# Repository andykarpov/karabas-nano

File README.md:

# Karabas-Nano

**Yet another ZX Spectrum clone ;)**

## Intro

ZX Spectrum compatible machine with real **Z80** CPU and all logic inside the CPLD Altera **EPM3256ATC144** (or EPM7512).

## The idea

The idea was to learn KiCAD and make a **cheapest** and **smallest** ZX Spectrum clone with minimum components and real CPU. 
Some parts of this schematics are grabbed from the **Karabas-128** and **ZX-UNO** projects (like RGB DAC, PAL coder, Tape-in logic).
The heart of this project is a real SMD Z80 CPU and ULA implementation on Altera CPLD EPM3256ATC144. 

## Firmwares

The board contains an SD card socket, so at least 2 different configurations are supported:

1) Z-Controller based configuration (Pentagon timings, GLUK reset service in the ROM bank 0, 1024kB of extended memory via port #DFFD (Profi))

2) DivMMC based configuration (Pentagon timings, ESXDOS 0.8.7 in the ROM bank 0, 128kB of memory)

## More info

**ERRATA for PCB rev.A:** [Russian](https://github.com/andykarpov/karabas-nano/blob/master/ERRATA_revA.md).

**ERRATA for PCB rev.B:** [Russian](https://github.com/andykarpov/karabas-nano/blob/master/ERRATA_revB.md).

**Latest revision:** rev.I.

License for this project is **WTFPL**. [More details here](https://github.com/andykarpov/karabas-nano/blob/master/LICENSE.md).

### Pre-production renders

### PCB Rev. H assembly example by [Xoomoh (Михайло Капітанов)](https://github.com/xoomoh/)

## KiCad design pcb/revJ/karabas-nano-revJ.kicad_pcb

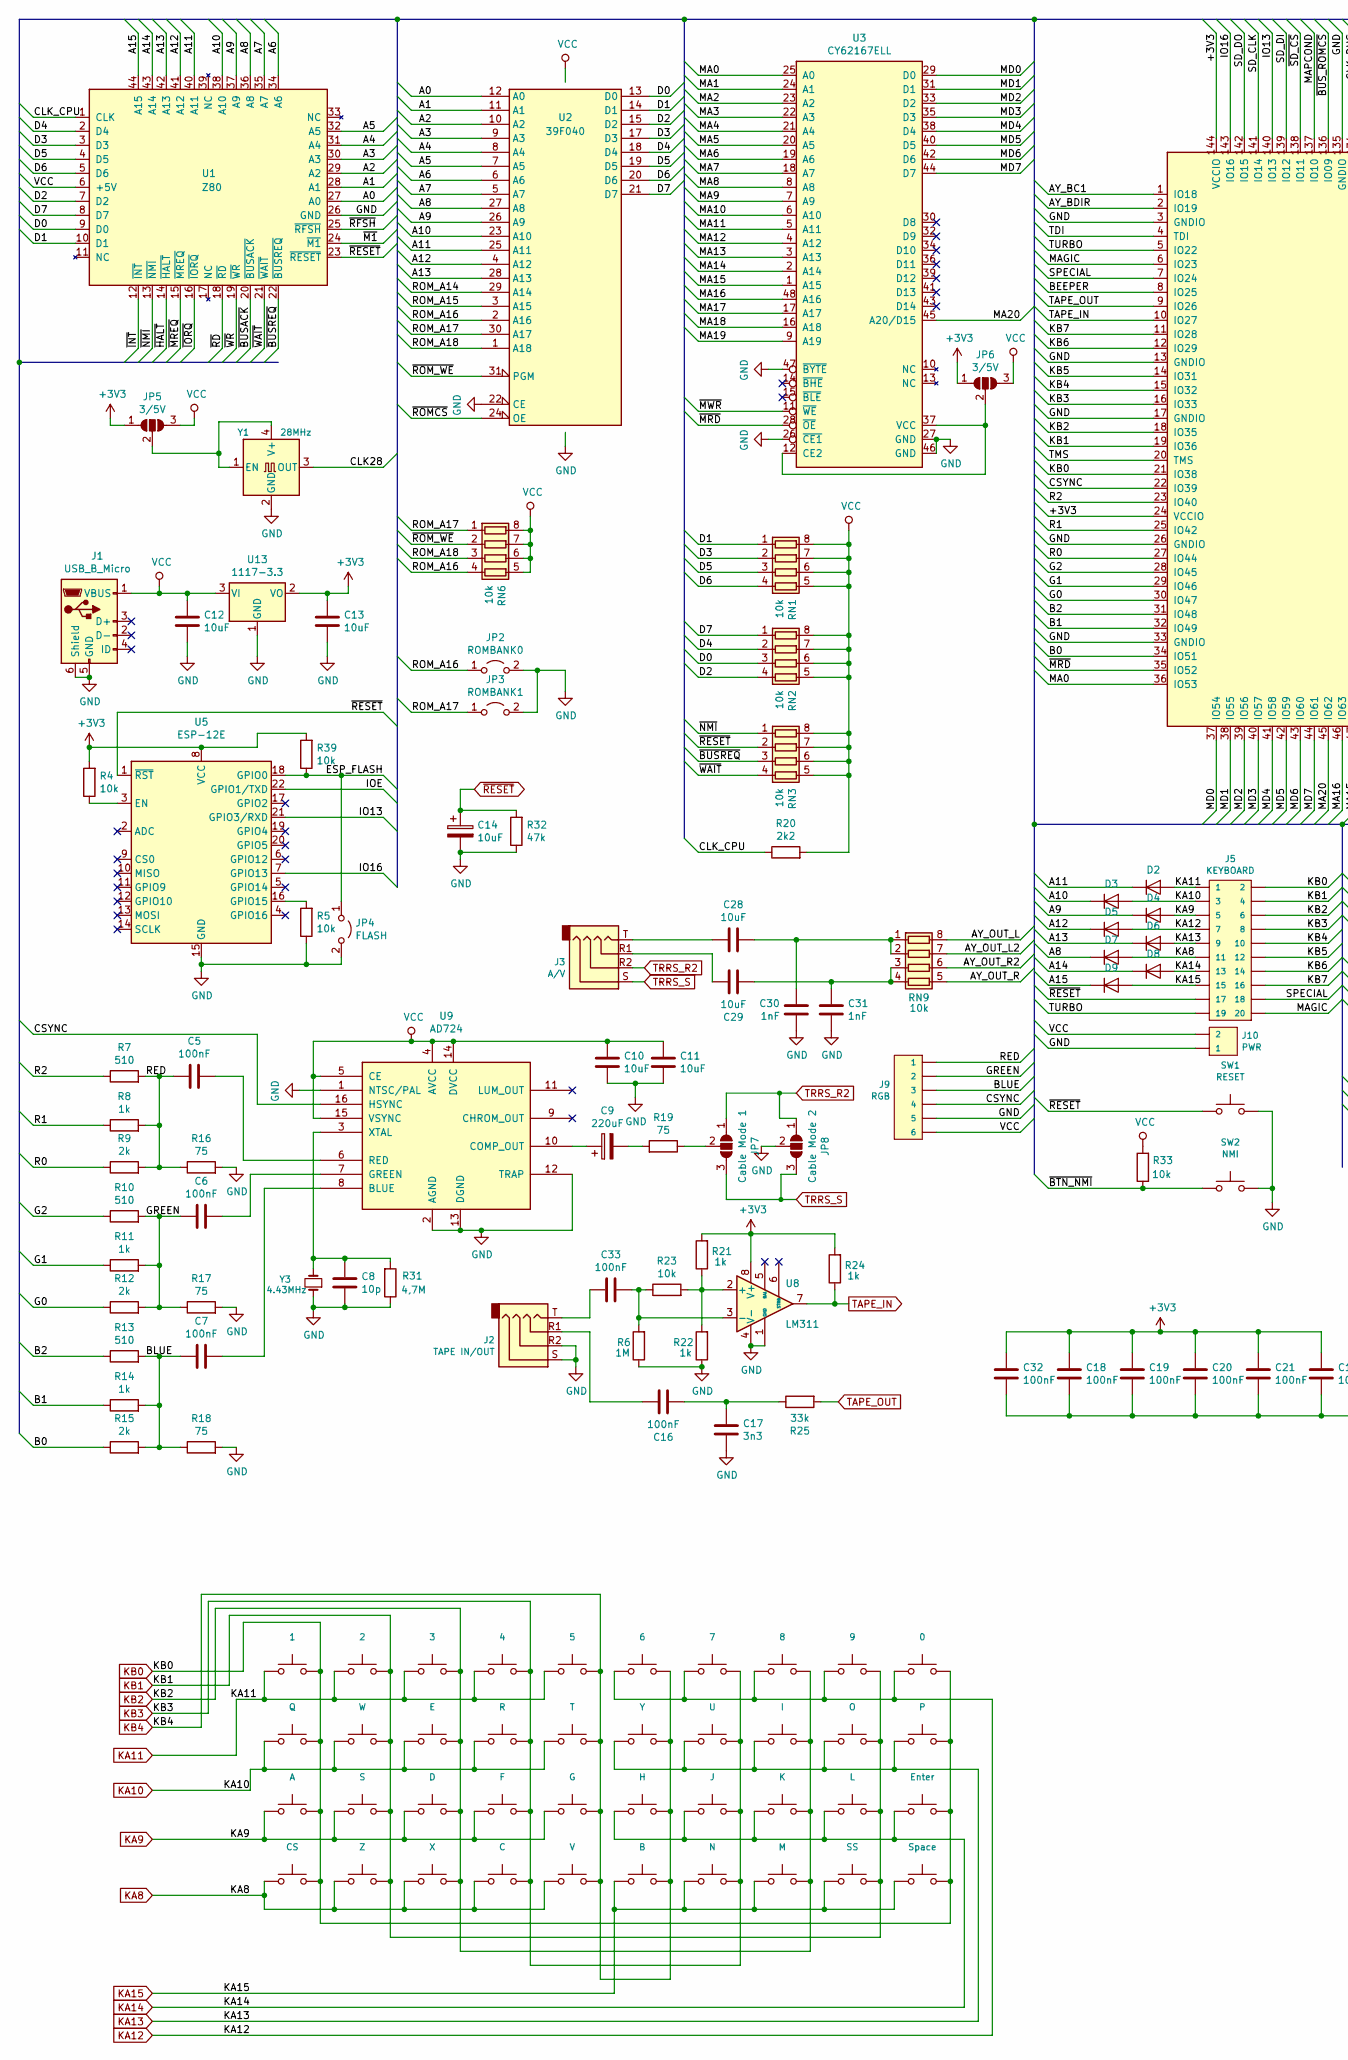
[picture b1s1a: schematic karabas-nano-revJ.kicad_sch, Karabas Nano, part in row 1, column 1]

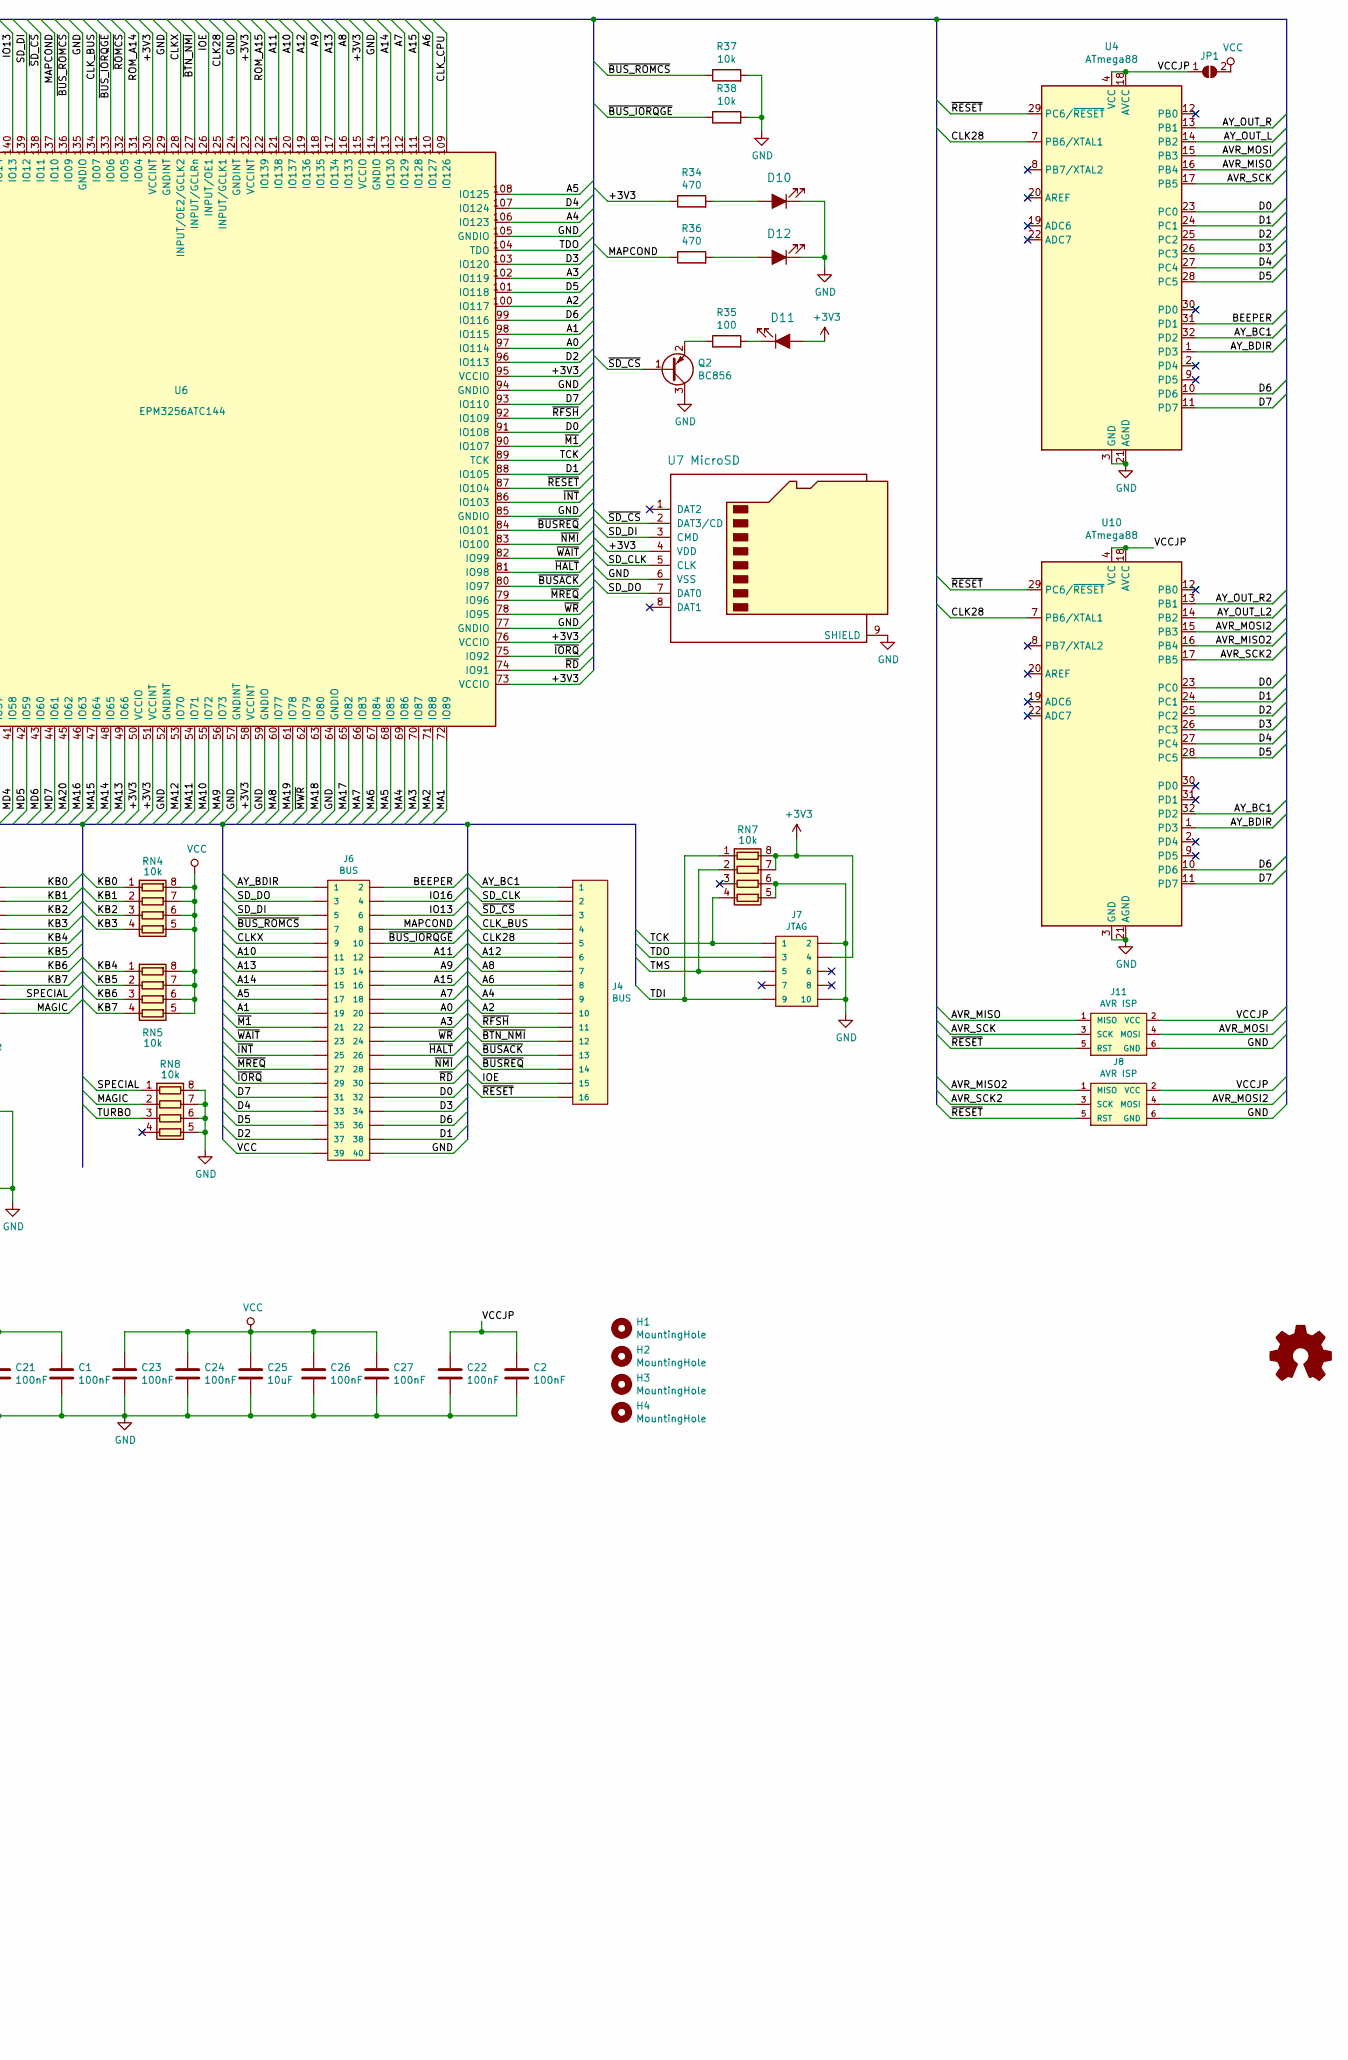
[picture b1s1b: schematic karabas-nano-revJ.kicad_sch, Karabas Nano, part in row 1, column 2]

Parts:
C1, C2, C5, C6, C7, C16, C18, C19, C20, C21, C22, C23, C24, C26, C27, C32, C33: 100nF; C_0805_2012Metric
C8: 10p; C_0805_2012Metric
C9: 220uF; CP_EIA-7343-31_Kemet-D_Pad2.25x2.55mm_HandSolder
C10, C11, C12, C13, C25, C28, C29: 10uF; C_0805_2012Metric
C14: 10uF; CP_EIA-3528-21_Kemet-B_Pad1.50x2.35mm_HandSolder
C17: 3n3; C_0805_2012Metric
C30, C31: 1nF; C_0805_2012Metric
D2, D3, D4, D5, D6, D7, D8, D9: 1N4148W; D_SOD-123
D10: PWR; LED_0805_2012Metric_Pad1.15x1.40mm_HandSolder; MPN LG R971-KN-1; Digi-Key_PN 475-1410-1-ND
D11: SD; LED_0805_2012Metric_Pad1.15x1.40mm_HandSolder; MPN LH R974-LP-1; Digi-Key_PN 475-1415-1-ND
D12: MMC; LED_0805_2012Metric_Pad1.15x1.40mm_HandSolder; MPN LH R974-LP-1; Digi-Key_PN 475-1415-1-ND
H1, H2, H3, H4: MountingHole; MountingHole_2.7mm_M2.5_Pad
J1: USB_B_Micro; USB_Micro-B_Amphenol_10118194_Horizontal
J2: TAPE IN/OUT; AUDIO_JACK_3.5MM_SMD_TRRS_rounded_mixed
J3: A/V; AUDIO_JACK_3.5MM_SMD_TRRS_rounded_mixed
J4: BUS; PinHeader_1x16_P2.54mm_Vertical
J5: KEYBOARD; PinHeader_2x10_P2.54mm_Vertical
J6: BUS; PinHeader_2x20_P2.54mm_Vertical
J7: JTAG; PinHeader_2x05_P2.54mm_Vertical
J8, J11: AVR ISP; PinHeader_2x03_P2.54mm_Vertical
J9: RGB; PinHeader_1x06_P2.54mm_Vertical
J10: PWR; PinHeader_1x02_P2.54mm_Vertical
JP1: SolderJumper_2_Open; SolderJumper-2_P1.3mm_Open_TrianglePad1.0x1.5mm
JP2: ROMBANK0; PinHeader_1x02_P2.54mm_Vertical
JP3: ROMBANK1; PinHeader_1x02_P2.54mm_Vertical
JP4: FLASH; PinHeader_1x02_P2.54mm_Vertical
JP5, JP6: 3/5V; SolderJumper-3_P1.3mm_Open_RoundedPad1.0x1.5mm
JP7: Cable Mode 1; SolderJumper-3_P1.3mm_Open_RoundedPad1.0x1.5mm
JP8: Cable Mode 2; SolderJumper-3_P1.3mm_Open_RoundedPad1.0x1.5mm
Q2: BC856; SOT-23
R4, R5, R23, R33, R37, R38, R39: 10k; R_0805_2012Metric
R6: 1M; R_0805_2012Metric
R7, R10, R13: 510; R_0805_2012Metric
R8, R11, R14, R21, R22, R24: 1k; R_0805_2012Metric
R9, R12, R15: 2k; R_0805_2012Metric
R16, R17, R18, R19: 75; R_0805_2012Metric
R20: 2k2; R_0805_2012Metric
R25: 33k; R_0805_2012Metric
R31: 4,7M; R_0805_2012Metric
R32: 47k; R_0805_2012Metric
R34, R36: 470; R_0805_2012Metric
R35: 100; R_0805_2012Metric
RN1, RN2, RN3, RN4, RN5, RN6, RN7, RN8, RN9: 10k; R_Array_Convex_4x0612
SW1: RESET; small-btn
SW2: NMI; small-btn
SW3: 1; small-btn
SW4: 2; small-btn
SW5: 3; small-btn
SW6: 4; small-btn
SW7: 5; small-btn
SW8: 6; small-btn
SW9: 7; small-btn
SW10: 8; small-btn
SW11: 9; small-btn
SW12: 0; small-btn
SW13: Q; small-btn
SW14: A; small-btn
SW15: CS; small-btn
SW16: W; small-btn
SW17: S; small-btn
SW18: Z; small-btn
SW19: E; small-btn
SW20: D; small-btn
SW21: X; small-btn
SW22: R; small-btn
SW23: F; small-btn
SW24: C; small-btn
SW25: T; small-btn
SW26: G; small-btn
SW27: V; small-btn
SW28: Y; small-btn
SW29: H; small-btn
SW30: B; small-btn
SW31: U; small-btn
SW32: J; small-btn
SW33: N; small-btn
SW34: I; small-btn
SW35: K; small-btn
SW36: M; small-btn
SW37: O; small-btn
SW38: L; small-btn
SW39: SS; small-btn
SW40: P; small-btn
SW41: Enter; small-btn
SW42: Space; small-btn
U1: Z80; TQFP-44_14x14mm_P0.8mm
U2: 39F040; PLCC-32_11.4x14.0mm_P1.27mm-bigpads
U3: CY62167ELL; TSOP-I-48_18.4x12mm_P0.5mm
U4, U10: ATmega88; TQFP-32_7x7mm_P0.8mm
U5: ESP-12E
U6: EPM3256ATC144; LQFP-144_20x20mm_P0.5mm
U7: MicroSD; Conn_uSDcard
U8: LM311; SO-8_3.9x4.9mm_P1.27mm
U9: AD724; SOIC-16W_7.5x10.3mm_P1.27mm
U13: 1117-3.3; SOT-223-3_TabPin2
Y1: 28MHz; Oscillator_SMD_EuroQuartz_XO91-4Pin_7.0x5.0mm
Y3: 4.43MHz; Crystal_HC49-U_Vertical

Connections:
+3V3: C1.2, C13.2, C18.2, C19.2, C20.2, C21.2, C32.2, D11.2 (A), J7.4, JP5.1 (A), JP6.1 (A), R4.2, R21.2, R24.2, R34.1, R39.2, RN7.7 (R2.2), RN7.8 (R1.2), U5.8 (VCC), U6.24 (VCCIO), U6.50 (VCCIO), U6.51 (VCCINT), U6.58 (VCCINT), U6.73 (VCCIO), U6.76 (VCCIO), U6.95 (VCCIO), U6.115 (VCCIO), U6.123 (VCCINT), U6.130 (VCCINT), U6.144 (VCCIO), U7.4 (VDD), U8.8 (V+), U13.2 (VO)
/A0: J6.20, U1.27 (A0), U2.12 (A0), U6.97 (IO114)
/A1: J6.19, U1.28 (A1), U2.11 (A1), U6.98 (IO115)
/A2: J4.10, U1.29 (A2), U2.10 (A2), U6.100 (IO117)
/A3: J6.22, U1.30 (A3), U2.9 (A3), U6.102 (IO119)
/A4: J4.9, U1.31 (A4), U2.8 (A4), U6.106 (IO123)
/A5: J6.17, U1.32 (A5), U2.7 (A5), U6.108 (IO125)
/A6: J4.8, U1.34 (A6), U2.6 (A6), U6.110 (IO127)
/A7: J6.18, U1.35 (A7), U2.5 (A7), U6.112 (IO129)
/A8: D7.1 (K), J4.7, U1.36 (A8), U2.27 (A8), U6.116 (IO133)
/A9: D4.1 (K), J6.14, U1.37 (A9), U2.26 (A9), U6.118 (IO135)
/A10: D3.1 (K), J6.11, U1.38 (A10), U2.23 (A10), U6.120 (IO137)
/A11: D2.1 (K), J6.12, U1.40 (A11), U2.25 (A11), U6.121 (IO138)
/A12: D5.1 (K), J4.6, U1.41 (A12), U2.4 (A12), U6.119 (IO136)
/A13: D6.1 (K), J6.13, U1.42 (A13), U2.28 (A13), U6.117 (IO134)
/A14: D8.1 (K), J6.15, U1.43 (A14), U6.113 (IO130)
/A15: D9.1 (K), J6.16, U1.44 (A15), U6.111 (IO128)
/AVR_MISO: J11.1 (MISO), U4.16 (PB4)
/AVR_MISO2: J8.1 (MISO), U10.16 (PB4)
/AVR_MOSI: J11.4 (MOSI), U4.15 (PB3)
/AVR_MOSI2: J8.4 (MOSI), U10.15 (PB3)
/AVR_SCK: J11.3 (SCK), U4.17 (PB5)
/AVR_SCK2: J8.3 (SCK), U10.17 (PB5)
/AY_BC1: J4.1, U4.32 (PD2), U6.1 (IO18), U10.32 (PD2)
/AY_BDIR: J6.1, U4.1 (PD3), U6.2 (IO19), U10.1 (PD3)
/AY_OUT_L: RN9.8 (R1.2), U4.14 (PB2)
/AY_OUT_L2: RN9.7 (R2.2), U10.14 (PB2)
/AY_OUT_R: RN9.5 (R4.2), U4.13 (PB1)
/AY_OUT_R2: RN9.6 (R3.2), U10.13 (PB1)
/B0: R15.1, U6.34 (IO51)
/B1: R14.1, U6.32 (IO49)
/B2: R13.1, U6.31 (IO48)
/BEEPER: J6.2, U4.31 (PD1), U6.8 (IO25)
/BLUE: C7.2, J9.3, R13.2, R14.2, R15.2, R18.1
/CLK28: J4.5, U4.7 (PB6/XTAL1), U6.125 (INPUT/GCLK1), U10.7 (PB6/XTAL1), Y1.3 (OUT)
/CLKX: J6.9, U6.128 (INPUT/OE2/GCLK2)
/CLK_BUS: J4.4, U6.134 (IO07)
/CLK_CPU: R20.1, U1.1 (CLK), U6.109 (IO126)
/CSYNC: J9.4, U6.22 (IO39), U9.16 (HSYNC)
/D0: J6.32, RN2.3 (R3.1), U1.9 (D0), U2.13 (D0), U4.23 (PC0), U6.91 (IO108), U10.23 (PC0)
/D1: J6.38, RN1.1 (R1.1), U1.10 (D1), U2.14 (D1), U4.24 (PC1), U6.88 (IO105), U10.24 (PC1)
/D2: J6.37, RN2.4 (R4.1), U1.7 (D2), U2.15 (D2), U4.25 (PC2), U6.96 (IO113), U10.25 (PC2)
/D3: J6.34, RN1.2 (R2.1), U1.3 (D3), U2.17 (D3), U4.26 (PC3), U6.103 (IO120), U10.26 (PC3)
/D4: J6.33, RN2.2 (R2.1), U1.2 (D4), U2.18 (D4), U4.27 (PC4), U6.107 (IO124), U10.27 (PC4)
/D5: J6.35, RN1.3 (R3.1), U1.4 (D5), U2.19 (D5), U4.28 (PC5), U6.101 (IO118), U10.28 (PC5)
/D6: J6.36, RN1.4 (R4.1), U1.5 (D6), U2.20 (D6), U4.10 (PD6), U6.99 (IO116), U10.10 (PD6)
/D7: J6.31, RN2.1 (R1.1), U1.8 (D7), U2.21 (D7), U4.11 (PD7), U6.93 (IO110), U10.11 (PD7)
/ESP_FLASH: JP4.1 (A), R39.1, U5.18 (GPIO0)
/G0: R12.1, U6.30 (IO47)
/G1: R11.1, U6.29 (IO46)
/G2: R10.1, U6.28 (IO45)
/GREEN: C6.2, J9.2, R10.2, R11.2, R12.2, R17.1
/IO13: J6.6, U5.21 (GPIO3/RXD), U6.140 (IO13)
/IO16: J6.4, U5.7 (GPIO13), U6.143 (IO16)
/IOE: J4.15, U5.22 (GPIO1/TXD), U6.126 (INPUT/OE1)
/KB5: J5.12, RN5.2 (R2.1), U6.14 (IO31)
/KB6: J5.14, RN5.3 (R3.1), U6.12 (IO29)
/KB7: J5.16, RN5.4 (R4.1), U6.11 (IO28)
/MA0: U3.25 (A0), U6.36 (IO53)
/MA1: U3.24 (A1), U6.72 (IO89)
/MA2: U3.23 (A2), U6.71 (IO88)
/MA3: U3.22 (A3), U6.70 (IO87)
/MA4: U3.21 (A4), U6.69 (IO86)
/MA5: U3.20 (A5), U6.68 (IO85)
/MA6: U3.19 (A6), U6.67 (IO84)
/MA7: U3.18 (A7), U6.66 (IO83)
/MA8: U3.8 (A8), U6.60 (IO77)
/MA9: U3.7 (A9), U6.56 (IO73)
/MA10: U3.6 (A10), U6.55 (IO72)
/MA11: U3.5 (A11), U6.54 (IO71)
/MA12: U3.4 (A12), U6.53 (IO70)
/MA13: U3.3 (A13), U6.49 (IO66)
/MA14: U3.2 (A14), U6.48 (IO65)
/MA15: U3.1 (A15), U6.47 (IO64)
/MA16: U3.48 (A16), U6.46 (IO63)
/MA17: U3.17 (A17), U6.65 (IO82)
/MA18: U3.16 (A18), U6.63 (IO80)
/MA19: U3.9 (A19), U6.61 (IO78)
/MA20: U3.45 (A20/D15), U6.45 (IO62)
/MAGIC: J5.20, RN8.2 (R2.1), U6.6 (IO23)
/MAPCOND: J6.8, R36.1, U6.137 (IO10)
/MD0: U3.29 (D0), U6.37 (IO54)
/MD1: U3.31 (D1), U6.38 (IO55)
/MD2: U3.33 (D2), U6.39 (IO56)
/MD3: U3.35 (D3), U6.40 (IO57)
/MD4: U3.38 (D4), U6.41 (IO58)
/MD5: U3.40 (D5), U6.42 (IO59)
/MD6: U3.42 (D6), U6.43 (IO60)
/MD7: U3.44 (D7), U6.44 (IO61)
/R0: R9.1, U6.27 (IO44)
/R1: R8.1, U6.25 (IO42)
/R2: R7.1, U6.23 (IO40)
/RED: C5.2, J9.1, R7.2, R8.2, R9.2, R16.1
/ROM_A14: U2.29 (A14), U6.131 (IO04)
/ROM_A15: U2.3 (A15), U6.122 (IO139)
/ROM_A16: JP2.1 (A), RN6.4 (R4.1), U2.2 (A16)
/ROM_A17: JP3.1 (A), RN6.1 (R1.1), U2.30 (A17)
/ROM_A18: RN6.3 (R3.1), U2.1 (A18)
/SD_CLK: J4.2, U6.141 (IO14), U7.5 (CLK)
/SD_DI: J6.5, U6.139 (IO12), U7.3 (CMD)
/SD_DO: J6.3, U6.142 (IO15), U7.7 (DAT0)
/SPECIAL: J5.18, RN8.1 (R1.1), U6.7 (IO24)
/TCK: J7.1, RN7.4 (R4.1), U6.89 (TCK)
/TDI: J7.9, RN7.1 (R1.1), U6.4 (TDI)
/TDO: J7.3, U6.104 (TDO)
/TMS: J7.5, RN7.2 (R2.1), U6.20 (TMS)
/TURBO: J5.19, RN8.3 (R3.1), U6.5 (IO22)
/VCCJP: C2.2, C22.2, J8.2 (VCC), J11.2 (VCC), JP1.1 (A), U4.4 (VCC), U4.6 (VCC), U4.18 (AVCC), U10.4 (VCC), U10.6 (VCC), U10.18 (AVCC)
/~BTN_NMI: J4.12, R33.1, SW2.1, U6.127 (INPUT/GCLRn)
/~BUSACK: J4.13, U1.20 (~BUSACK), U6.80 (IO97)
/~BUSREQ: J4.14, RN3.3 (R3.1), U1.22 (~BUSREQ), U6.84 (IO101)
/~BUS_IORQGE: J6.10, R38.1, U6.133 (IO06)
/~BUS_ROMCS: J6.7, R37.1, U6.136 (IO09)
/~HALT: J6.26, U1.14 (~HALT), U6.81 (IO98)
/~INT: J6.25, U1.12 (~INT), U6.86 (IO103)
/~IORQ: J6.29, U1.16 (~IORQ), U6.75 (IO92)
/~M1: J6.21, U1.24 (~M1), U6.90 (IO107)
/~MRD: U3.28 (~OE), U6.35 (IO52)
/~MREQ: J6.27, U1.15 (~MREQ), U6.79 (IO96)
/~MWR: U3.11 (~WE), U6.62 (IO79)
/~NMI: J6.28, RN3.1 (R1.1), U1.13 (~NMI), U6.83 (IO100)
/~RD: J6.30, U1.18 (~RD), U6.74 (IO91)
/~RFSH: J4.11, U1.25 (~RFSH), U6.92 (IO109)
/~ROMCS: U2.24 (OE), U6.132 (IO05)
/~ROM_WE: RN6.2 (R2.1), U2.31 (PGM)
/~SD_CS: J4.3, Q2.1 (B), U6.138 (IO11), U7.2 (DAT3/CD)
/~WAIT: J6.23, RN3.4 (R4.1), U1.21 (~WAIT), U6.82 (IO99)
/~WR: J6.24, U1.19 (~WR), U6.78 (IO95)
GND: C1.1, C2.1, C8.1, C10.1, C11.1, C12.1, C13.1, C14.2, C17.1, C18.1, C19.1, C20.1, C21.1, C22.1, C23.1, C24.1, C25.1, C26.1, C27.1, C30.1, C31.1, C32.1, D10.1 (K), D12.1 (K), J1.5 (GND), J1.6 (Shield), J2.R2, J2.S, J6.40, J7.2, J7.10, J8.6 (GND), J9.5, J10.1, J11.6 (GND), JP2.2 (B), JP3.2 (B), JP4.2 (B), JP8.2 (C), Q2.3 (C), R5.1, R6.1, R16.2, R17.2, R18.2, R22.1, R31.1, R32.1, R37.2, R38.2, RN7.5 (R4.2), RN7.6 (R3.2), RN8.5 (R4.2), RN8.6 (R3.2), RN8.7 (R2.2), RN8.8 (R1.2), SW1.2, SW2.2, U1.26 (GND), U2.16 (GND), U2.22 (CE), U3.26 (~CE1), U3.27 (GND), U3.46 (GND), U3.47 (~BYTE), U4.3 (GND), U4.5 (GND), U4.21 (AGND), U5.15 (GND), U6.3 (GNDIO), U6.13 (GNDIO), U6.17 (GNDIO), U6.26 (GNDIO), U6.33 (GNDIO), U6.52 (GNDINT), U6.57 (GNDINT), U6.59 (GNDIO), U6.64 (GNDIO), U6.77 (GNDIO), U6.85 (GNDIO), U6.94 (GNDIO), U6.105 (GNDIO), U6.114 (GNDIO), U6.124 (GNDINT), U6.129 (GNDINT), U6.135 (GNDIO), U7.6 (VSS), U7.9 (SHIELD), U8.1 (GND), U8.4 (V-), U9.1 (NTSC/PAL), U9.2 (AGND), U9.12 (TRAP), U9.13 (DGND), U10.3 (GND), U10.5 (GND), U10.21 (AGND), U13.1 (GND), Y1.2 (GND), Y3.1
KA8: D7.2 (A), J5.11, SW15.1, SW18.1, SW21.1, SW24.1, SW27.1
KA9: D4.2 (A), J5.5, SW14.1, SW17.1, SW20.1, SW23.1, SW26.1
KA10: D3.2 (A), J5.3, SW13.1, SW16.1, SW19.1, SW22.1, SW25.1
KA11: D2.2 (A), J5.1, SW3.1, SW4.1, SW5.1, SW6.1, SW7.1
KA12: D5.2 (A), J5.7, SW8.1, SW9.1, SW10.1, SW11.1, SW12.1
KA13: D6.2 (A), J5.9, SW28.1, SW31.1, SW34.1, SW37.1, SW40.1
KA14: D8.2 (A), J5.13, SW29.1, SW32.1, SW35.1, SW38.1, SW41.1
KA15: D9.2 (A), J5.15, SW30.1, SW33.1, SW36.1, SW39.1, SW42.1
KB0: J5.2, RN4.1 (R1.1), SW3.2, SW12.2, SW13.2, SW14.2, SW15.2, SW40.2, SW41.2, SW42.2, U6.21 (IO38)
KB1: J5.4, RN4.2 (R2.1), SW4.2, SW11.2, SW16.2, SW17.2, SW18.2, SW37.2, SW38.2, SW39.2, U6.19 (IO36)
KB2: J5.6, RN4.3 (R3.1), SW5.2, SW10.2, SW19.2, SW20.2, SW21.2, SW34.2, SW35.2, SW36.2, U6.18 (IO35)
KB3: J5.8, RN4.4 (R4.1), SW6.2, SW9.2, SW22.2, SW23.2, SW24.2, SW31.2, SW32.2, SW33.2, U6.16 (IO33)
KB4: J5.10, RN5.1 (R1.1), SW7.2, SW8.2, SW25.2, SW26.2, SW27.2, SW28.2, SW29.2, SW30.2, U6.15 (IO32)
unnamed: C5.1, U9.6 (RED)
unnamed: C6.1, U9.7 (GREEN)
unnamed: C7.1, U9.8 (BLUE)
unnamed: C8.2, R31.2, U9.3 (XTAL), Y3.2
unnamed: C9.1, U9.10 (COMP_OUT)
unnamed: C9.2, R19.2
unnamed: C16.1, C17.2, R25.1
unnamed: C16.2, J2.R1
unnamed: C28.1, C30.2, RN9.1 (R1.1), RN9.2 (R2.1)
unnamed: C28.2, J3.T
unnamed: C29.1, C31.2, RN9.3 (R3.1), RN9.4 (R4.1)
unnamed: C29.2, J3.R1
unnamed: C33.1, R6.2, R23.1, U8.3 (-)
unnamed: C33.2, J2.T
unnamed: D10.2 (A), R34.2
unnamed: D11.1 (K), R35.2
unnamed: D12.2 (A), R36.2
unnamed: JP5.2 (C), Y1.1 (EN), Y1.4 (V+)
unnamed: JP6.2 (C), U3.12 (CE2), U3.37 (VCC)
unnamed: Q2.2 (E), R35.1
unnamed: R4.1, U5.3 (EN)
unnamed: R5.2, U5.16 (GPIO15)
unnamed: JP7.2 (C), R19.1
unnamed: R21.1, R22.2, R23.2, U8.2 (+)
TAPE_IN: R24.1, U6.10 (IO27), U8.7
TAPE_OUT: R25.2, U6.9 (IO26)
TRRS_R2: J3.R2, JP7.1 (A), JP8.1 (A)
TRRS_S: J3.S, JP7.3 (B), JP8.3 (B)
VCC: C10.2, C11.2, C12.2, C23.2, C24.2, C25.2, C26.2, C27.2, J1.1 (VBUS), J6.39, J9.6, J10.2, JP1.2 (B), JP5.3 (B), JP6.3 (B), R20.2, R33.2, RN1.5 (R4.2), RN1.6 (R3.2), RN1.7 (R2.2), RN1.8 (R1.2), RN2.5 (R4.2), RN2.6 (R3.2), RN2.7 (R2.2), RN2.8 (R1.2), RN3.5 (R4.2), RN3.6 (R3.2), RN3.7 (R2.2), RN3.8 (R1.2), RN4.5 (R4.2), RN4.6 (R3.2), RN4.7 (R2.2), RN4.8 (R1.2), RN5.5 (R4.2), RN5.6 (R3.2), RN5.7 (R2.2), RN5.8 (R1.2), RN6.5 (R4.2), RN6.6 (R3.2), RN6.7 (R2.2), RN6.8 (R1.2), U1.6 (+5V), U2.32 (VCC), U9.4 (AVCC), U9.5 (CE), U9.14 (DVCC), U9.15 (VSYNC), U13.3 (VI)
~RESET: C14.1, J4.16, J5.17, J8.5 (RST), J11.5 (RST), R32.2, RN3.2 (R2.1), SW1.1, U1.23 (~RESET), U4.29 (PC6/~RESET), U5.1 (~RST), U6.87 (IO104), U10.29 (PC6/~RESET)

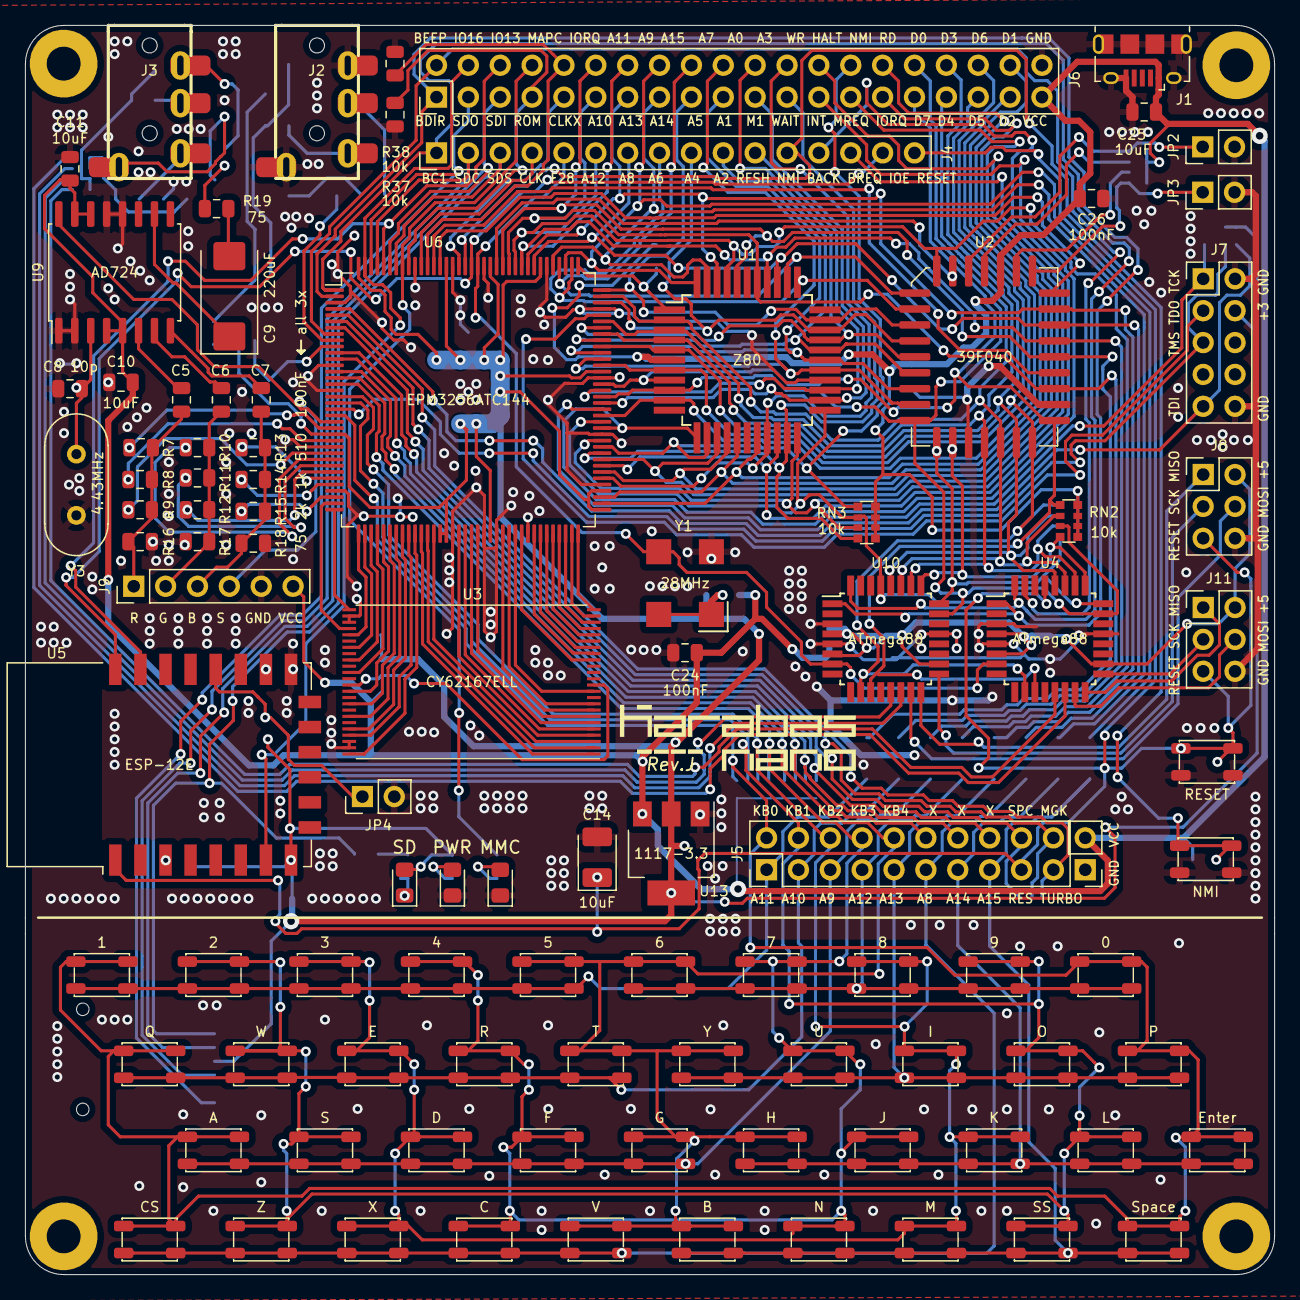
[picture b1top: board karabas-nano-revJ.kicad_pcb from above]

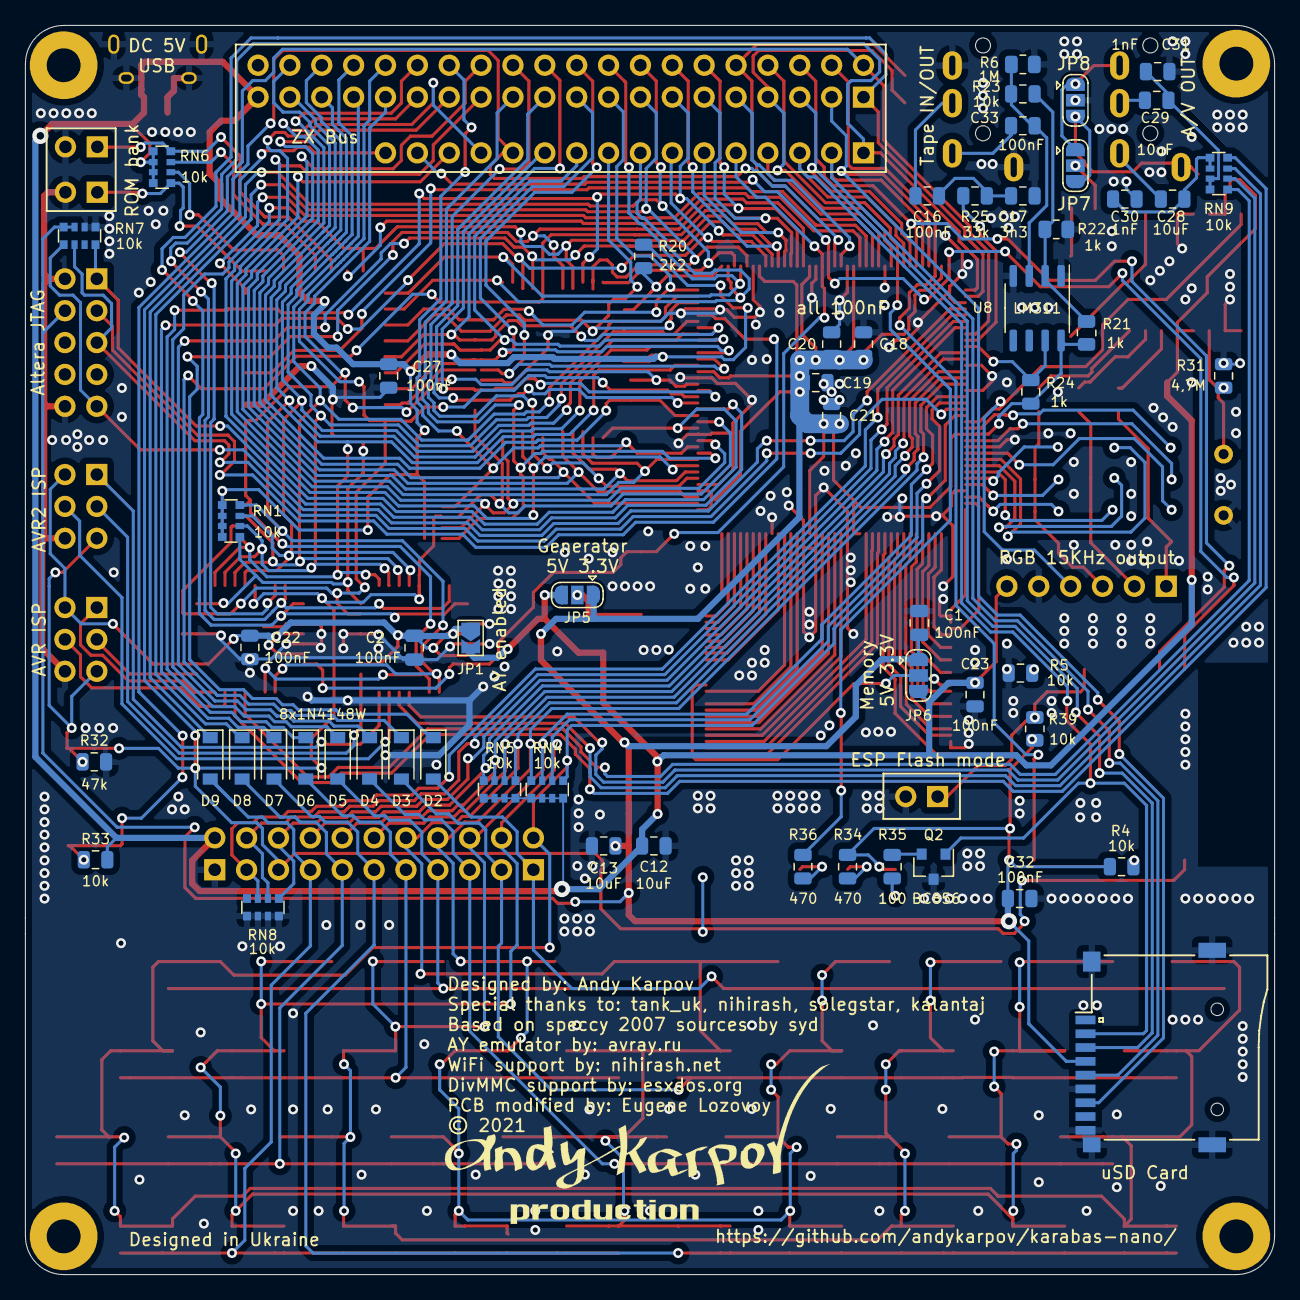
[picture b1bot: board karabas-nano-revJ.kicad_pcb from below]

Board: 2 copper layers, 99.6 x 99.6 mm, 160 parts (58 on the bottom side), 172 nets.

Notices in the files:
firmware/revCmmc/karabas_nano_revCmmc.qsf:
Copyright (C) 1991-2013 Altera Corporation
pcb/revJ/karabas-nano-revJ.kicad_pcb:
© 2021
